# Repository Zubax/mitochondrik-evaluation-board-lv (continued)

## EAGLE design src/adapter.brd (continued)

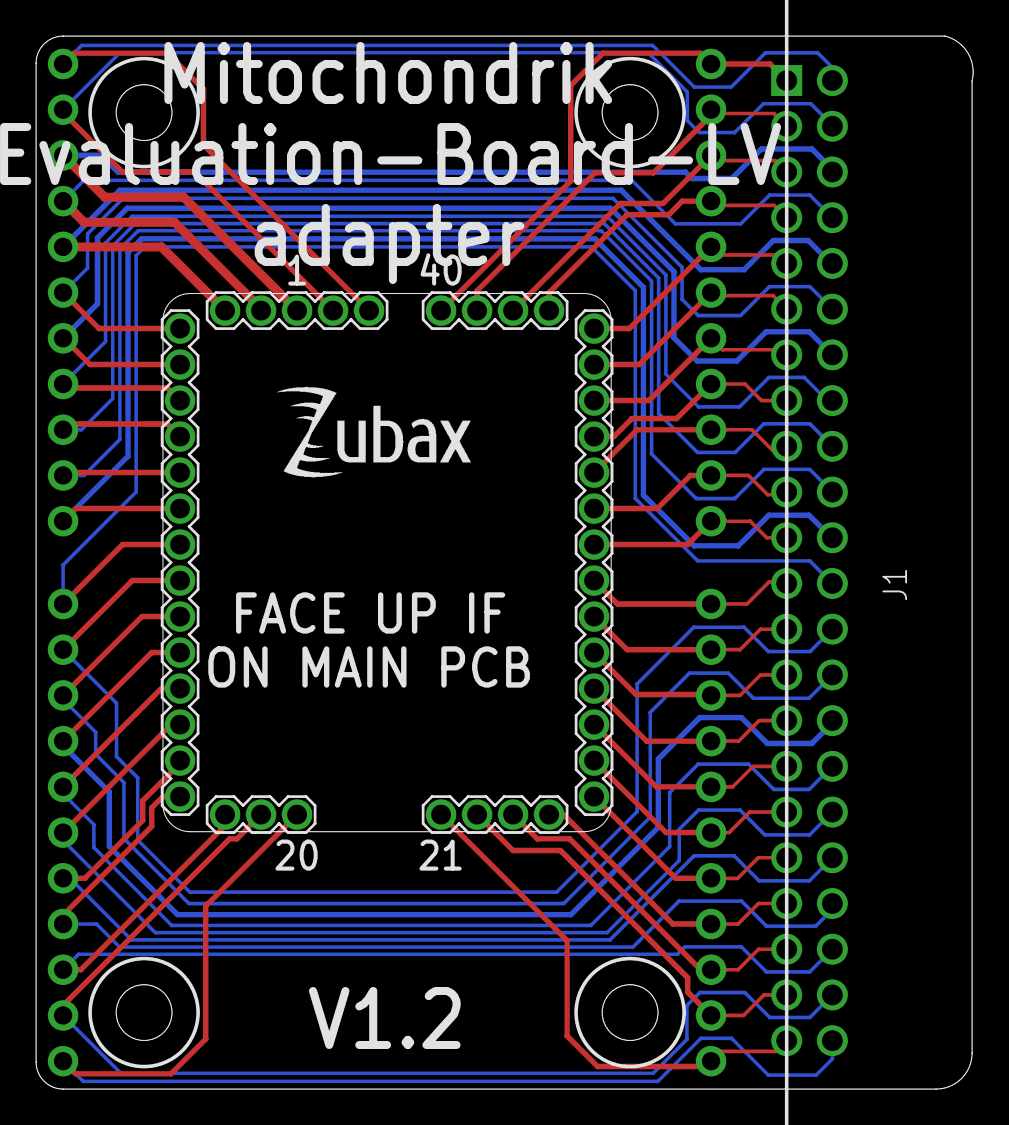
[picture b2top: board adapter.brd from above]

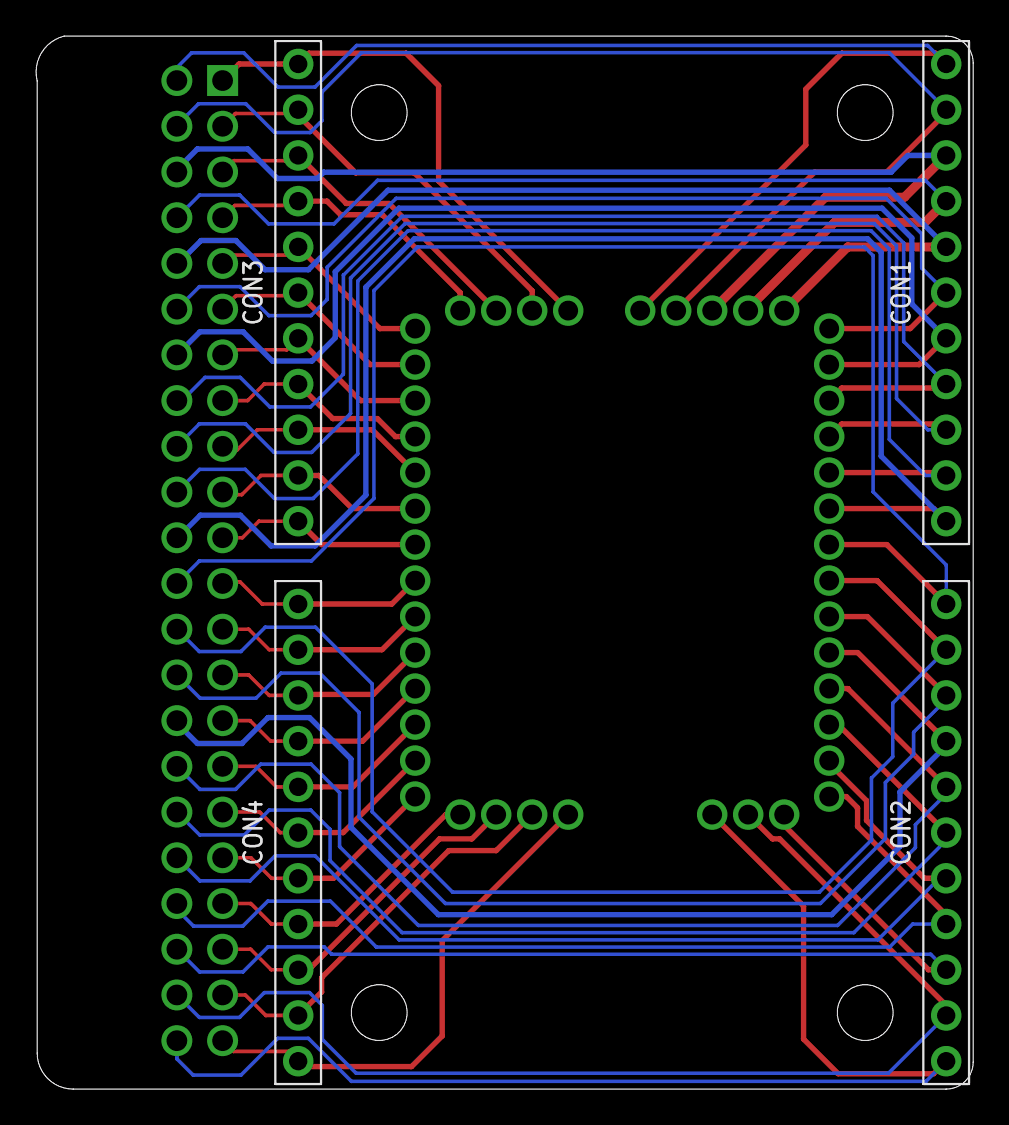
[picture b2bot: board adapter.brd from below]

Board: 2 copper layers, 52.1 x 58.5 mm, 7 parts (4 on the bottom side), 44 nets.

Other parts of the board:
U$2: ZUBAX_LOGO_5X10

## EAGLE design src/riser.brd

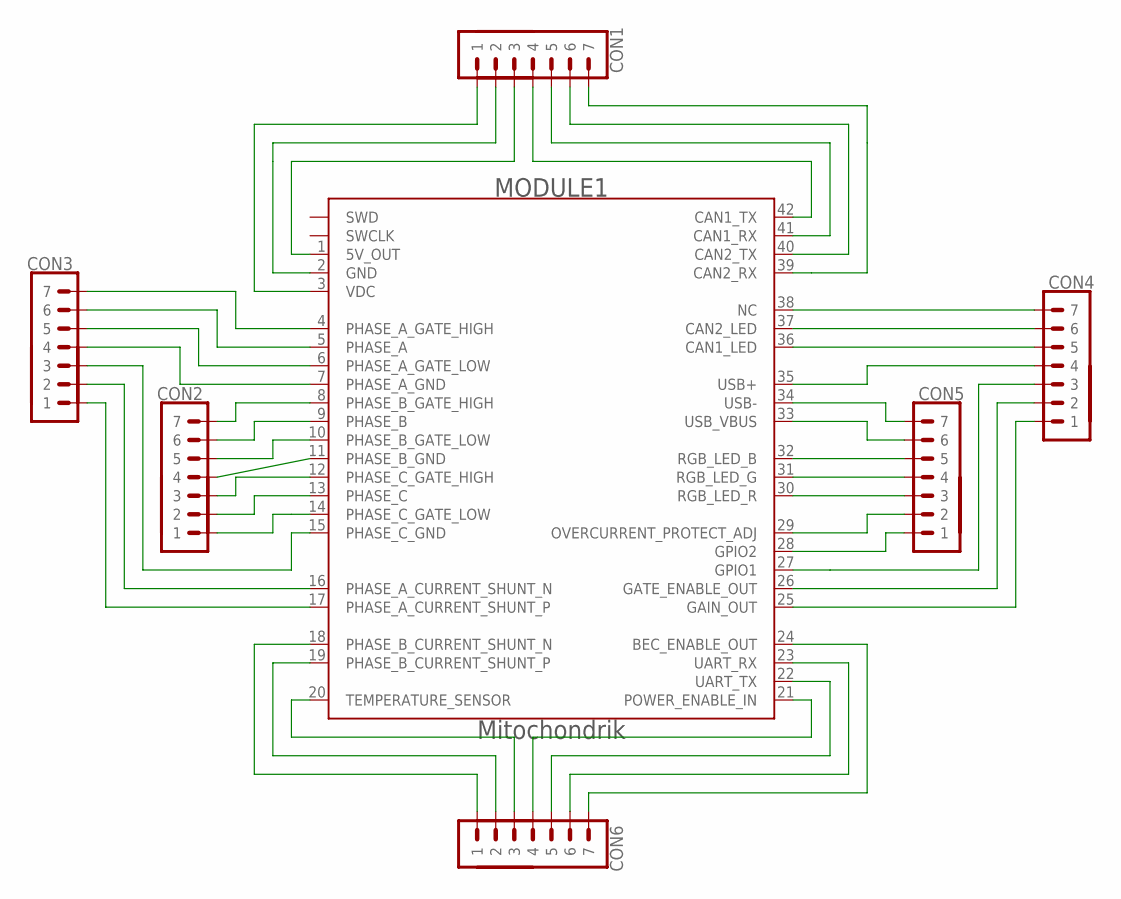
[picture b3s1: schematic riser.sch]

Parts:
CON1, CON2, CON3, CON4, CON5, CON6: PINHEAD_1X07-2; 1X07-PTH-2
MODULE1: MITOHONDRIQUE_POGO-POGO; MITOHONDRIQUE-POGO

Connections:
unnamed: CON1.7, MODULE1.39 (CAN2_RX)
unnamed: CON1.6, MODULE1.40 (CAN2_TX)
unnamed: CON1.5, MODULE1.41 (CAN1_RX)
unnamed: CON1.4, MODULE1.42 (CAN1_TX)
unnamed: CON1.3, MODULE1.1 (5V_OUT)
unnamed: CON1.2, MODULE1.2 (GND)
unnamed: CON1.1, MODULE1.3 (VDC)
unnamed: CON6.7, MODULE1.24 (BEC_ENABLE_OUT)
unnamed: CON6.6, MODULE1.23 (UART_RX)
unnamed: CON6.5, MODULE1.22 (UART_TX)
unnamed: CON6.4, MODULE1.21 (POWER_ENABLE_IN)
unnamed: CON6.3, MODULE1.20 (TEMPERATURE_SENSOR)
unnamed: CON6.2, MODULE1.19 (PHASE_B_CURRENT_SHUNT_P)
unnamed: CON6.1, MODULE1.18 (PHASE_B_CURRENT_SHUNT_N)
unnamed: CON3.7, MODULE1.4 (PHASE_A_GATE_HIGH)
unnamed: CON3.6, MODULE1.5 (PHASE_A)
unnamed: CON3.4, MODULE1.7 (PHASE_A_GND)
unnamed: CON3.5, MODULE1.6 (PHASE_A_GATE_LOW)
unnamed: CON3.1, MODULE1.17 (PHASE_A_CURRENT_SHUNT_P)
unnamed: CON3.2, MODULE1.16 (PHASE_A_CURRENT_SHUNT_N)
unnamed: CON3.3, MODULE1.15 (PHASE_C_GND)
unnamed: CON2.1, MODULE1.14 (PHASE_C_GATE_LOW)
unnamed: CON2.2, MODULE1.13 (PHASE_C)
unnamed: CON2.3, MODULE1.12 (PHASE_C_GATE_HIGH)
unnamed: CON2.4, MODULE1.11 (PHASE_B_GND)
unnamed: CON2.5, MODULE1.10 (PHASE_B_GATE_LOW)
unnamed: CON4.7, MODULE1.38 (NC)
unnamed: CON2.7, MODULE1.8 (PHASE_B_GATE_HIGH)
unnamed: CON2.6, MODULE1.9 (PHASE_B)
unnamed: CON4.6, MODULE1.37 (CAN2_LED)
unnamed: CON4.5, MODULE1.36 (CAN1_LED)
unnamed: CON4.3, MODULE1.27 (GPIO1)
unnamed: CON4.4, MODULE1.35 (USB+)
unnamed: CON4.2, MODULE1.26 (GATE_ENABLE_OUT)
unnamed: CON4.1, MODULE1.25 (GAIN_OUT)
unnamed: CON5.1, MODULE1.28 (GPIO2)
unnamed: CON5.2, MODULE1.29 (OVERCURRENT_PROTECT_ADJ)
unnamed: CON5.3, MODULE1.30 (RGB_LED_R)
unnamed: CON5.4, MODULE1.31 (RGB_LED_G)
unnamed: CON5.5, MODULE1.32 (RGB_LED_B)
unnamed: CON5.6, MODULE1.33 (USB_VBUS)
unnamed: CON5.7, MODULE1.34 (USB-)
SWCLK: MODULE1.SWCLK
SWD: MODULE1.SWDIO (SWD)

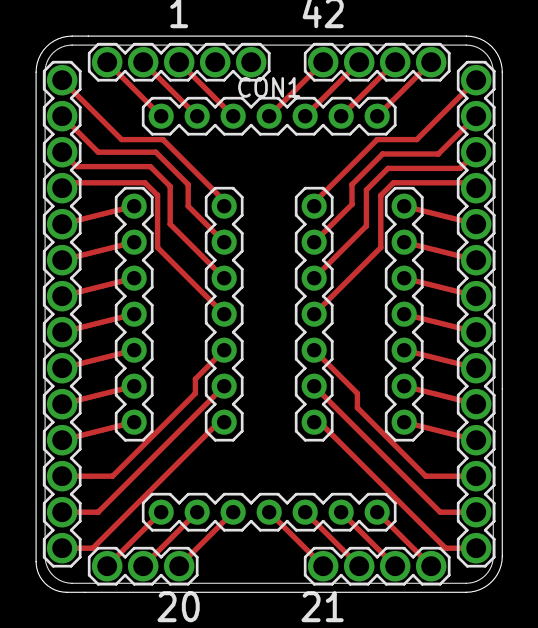
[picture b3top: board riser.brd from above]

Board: 2 copper layers, 25.9 x 30.9 mm, 7 parts (0 on the bottom side), 42 nets.

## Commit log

2020-12-21 Initial import
2020-12-28 USB PLS connector placement fixed
2020-12-28 Attribute updates for cheap manufacturability
2020-12-28 Massive attribute updates
2020-12-28 Libraries update
2020-12-28 BOM updates
2021-01-05 Pictures
2021-01-06 1-wire EEPROM added to CAN1 LED line in case it will be some day implemented in firmware
2021-01-08 solder joint for termination resistors for CAN buses added
2021-01-08 Additional TVS diode footprint added
2021-01-11 Silkscreen update
2021-01-11 Adapter PCB added
2021-01-11 attribute updates
2021-01-13 Manufacturing instructions added
2021-01-13 Unnecessary component removed
2021-01-18 MOSFETs replaced
2021-01-20 additional drawings
2021-01-20 Mito footprint update
2021-01-20 All the pictures moved to one folder
2021-01-20 naming
2021-01-21 Proofread the docs without changing the semantics
2021-01-22 Proofread the docs without changing the semantics (#1)
2021-01-27 Update JIG.brd
    Couple mounting holes for Babel-Babel plastic mount added.
2021-01-28 USB connector type updated
2021-01-29 Resistor values updated
2021-01-29 Massive attribute update
2021-02-04 renaming
2021-02-04 connectors attribute updates
2021-02-04 CAM and DRU files added
2021-02-10 Massive attribute update (#3)
    * Massive attribute update
    * renaming
    * connectors attribute updates
    * CAM and DRU files added
2021-07-28 usb pinout fix #5
2021-07-28 fixes to issue #4
2021-07-29 usb vbus trace width fix
2021-07-29 usb pinout fix #5 (#8)
    * usb pinout fix #5
    * fixes to issue #4
    * usb vbus trace width fix
2021-08-04 repo restructered
2021-08-05 * repo restructured * README.md updated
2021-08-05 Create flashing
2021-08-05 Rename flashing to flashing.md
2021-08-06 folder figures moved to folder doc README doc updated manufacturing doc updated
2021-08-06 Create LICENSE
2021-08-06 BOM table added in manufacturing instructions
2021-08-13 README.md updated
2021-08-16 First release (#9)
    * repo restructered
    * * repo restructured
    * README.md updated
    * Update manufacturing.md
    * Update manufacturing.md
    * Update manufacturing.md
2023-02-17 bug fix
2023-02-17 sync
2023-02-17 update changelog
2023-02-17 protection diode added to CANVDD
2023-02-17 bug fix (#14)
    * bug fix
    * sync
    * update changelog
    * protection diode added to CANVDD
2023-02-17 screw terminal added
2023-02-21 new holder added
2023-02-21 change in 3d parts
2023-03-02 holder model updated
2023-03-03 holder redesigned
2023-03-03 added connector to adapter
2023-03-03 screw terminal added (#16)
    * screw terminal added
    * new holder added
    * change in 3d parts
    * holder model updated
    * holder redesigned
    * added connector to adapter
2023-03-03 added missing part numbers
2023-03-03 added missing part numbers (#17)
2023-03-10 FET replaced
2023-03-10 FET replaced (#19)
2023-03-10 silkscreen
2023-03-10 silkscreen (#20)
2023-03-10 variant_fix
2023-03-10 variant_fix (#21)
2023-04-27 Myduck to MEB
    - changed Myduck to Mitochondrik Evaluation Board
    - added assembly photos
    still need to finish updating the asssembly guide
2023-05-02 updated manufacturing instructions for v1.2
2023-05-02 removed silkscreen
    closes #23
2023-05-03 3D source files for pogo jig
2023-05-03 updated assembly guide
2023-05-06 Update MEB-LV.brd
    Flipping J4 from bottom side to the top side in MEB-LV.brd
2023-05-08 Update MEB-LV.brd (#26)
    Flipping J4 from bottom side to the top side in MEB-LV.brd
2023-05-09 requested changes
2023-05-10 v1.2 assembly (#25)
    closes #18 - will change repo name to MEB-LV once this is merged
    closes #23
    closes #22 - @abualkasim-bakeer did it
    ---------
2023-06-16 changes for v1.2
    created new pogo jig - changed height to 5.5mm to account for ribbon connectors (option 1), closes #39
    removed legs in pogo jig, closes #31
    removed wings for the top 3D part, closes #30
    added countersunk holes for 3D parts, closes #32
    updated assembly instructions, closes #29
    moved power terminal silkscreen labels so they are seen, closes #33
2023-06-16 updated pogo jig
    made the holes bigger & added holes for testpoints
2023-06-20 added RGB LED instructions
    closes #41
2023-06-20 updated 3D holders
    reduced magnet distance
    added steel sheet slot
    widened screw holes to 3.4 mm
2023-07-12 updated 3D bottom holder
    added triangle stub to ensure proper orientation of the Mitochondrik during flashing
2023-07-19 Updated manufacturing instructions
2023-07-20 Updated manufacturing instructions
    according to comments
2023-08-01 changes requested
2023-08-01 changes for v1.2 (#40)
    created new pogo jig - changed height to 5.5mm to account for ribbon
    connectors (option 1), closes #39
    removed legs in pogo jig, closes #31
    removed wings for the top 3D part, closes #30
    added countersunk holes for 3D parts, closes #32
    updated assembly instructions, closes #29
